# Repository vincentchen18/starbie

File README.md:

# Starbie

## Overview

Starbie is a tiny motion controlled desktop pet, powered by USB or battery. It is a star-shaped PCB hosting a little digital creature on an OLED Screen. It includes multiple interactive functionalities. Tilt it to navigate menus, shake it to wake it up, and watch its mood light change as you neglect it. (you probably shouldn't neglect it but this is also a functionality, not a recommendation.) Also has multiple sensors that track gyroscopic and accelerometric position, as well as tracking temperature and humidity.

This project was built for Hack Club's hardware program [Half Life](https://halflife.hackclub.com/), a 10 week YSWS to help beginners learn hardware project, and incidentally, it is ***my*** first hardware project!!! :DDD

I will also note that this is based off a tutorial from one of Half Life's organisers, and you can find the tutorial repo [here](https://github.com/SharKingStudios/Starbie). I added some additional features myself, but thank you [SharKingStudios](https://github.com/SharKingStudios/) this tutorial as it was a great starting point.

Additionally, I have also created a storage case for Starbie (although it is irregularly shaped due to how I shaped the printed circuit board)

## Schematic, PCB and Components

The final schematic is shown in the above picture, featuring a XIAO-ESP32-C3, Environment and MPU6050 sensor, as well as a menu button and an on/off switch as well as a battery connector. 

The desktop pet can be powered both by battery or by USB connection

## Features

- **Wandering pet:** a 32×32 pixel creature walks across the OLED.
- **Tilt-controlled radial menu:** press the menu button, then tilt to pick an option, and press again to select the option. The interactive options are:
- --> **Nap:** Starbie just falls asleep with zzz's until you shake it to wake it up
- --> **Play:** Starbie sprints in laps with hearts
- --> **Feed:** Starbie wiggles and jumps and gains fullness
- --> **Pet:** Increases Starbie's joy
- **Stats:** Joy, Energy, and Fullness, saved to flash so they save when you turn Starbie back on
- **Shake to wake:** shaking it wakes it and gets a reaction
- **Environment sensing:** Starbie can detect the temperature (and it **will** complain if it's too hot or cold!)
- **RGB Mood Light**: this shows how starbie is feeling:
Dark blue: napping
Pink: being loved
Red: too hot!
ice blue: too cold!
amber: hungry or tired
green: happy (brighter = morer happierness)
purple: dizzy

## Hardware

A storage case for Starbie has also been included, and you can find the box and lid STEP files in [`3D Models`](3D%20Models/)

Full list in [`BOM.csv`](Starbie/BOM.csv). Gerbers in [`gerbers/`](Starbie/gerbers/).

## Firmware

Arduino IDE was used to program Starbie.

## AI Usage

AI was not used in any way for this project besides as a guide to help me learn to use KiCad

## Bill of Materials

### Grant-funded ($30 tier 1)

| Item | Purpose | Qty | Unit (USD) | Total (USD) | Link |
|---|---|---|---|---|---|
| Starbie PCB (2-layer, 97.3×140.3mm) | Custom star-shaped board | 5 | 2.12 | 10.60 | [JLCPCB](https://jlcpcb.com/quote) |
| JLCPCB New User PCB coupon | Discount | 1 | -6.00 | -6.00 | — |
| JLCPCB shipping (Global Standard Direct Line → AU) | Shipping | 1 | 8.52 | 8.52 | [JLCPCB](https://jlcpcb.com/quote) |
| Seeed Studio XIAO ESP32-C3 | Main microcontroller | 1 | 6.31 | 6.31 | [AliExpress](https://www.aliexpress.com/item/1005008791664713.html) |
| 0.96" 128×64 I2C OLED (SSD1306) | Display | 1 | 2.20 | 2.20 | [AliExpress](https://www.aliexpress.com/item/1005006262908701.html) |
| DHT11 (bare 4-pin) | Temp + humidity sensor | 1 | 1.60 | 1.60 | [AliExpress](https://www.aliexpress.com/item/1005008818897051.html) |
| MPU-6050 (GY-521) | Accelerometer/gyro for tilt + shake | 1 | 1.03 | 1.03 | [AliExpress](https://www.aliexpress.com/item/1005008604349573.html) |
| 5mm RGB LED, common cathode (pack) | Mood light | 1 | 2.17 | 2.17 | [AliExpress](https://www.aliexpress.com/item/32601543257.html) |
| Resistor kit, 1/4W 300pcs (10k + 220Ω used) | DHT11 pull-up + LED current limiting | 1 | 3.23 | 3.23 | [AliExpress](https://www.aliexpress.com/item/1005011772534173.html) |
| **Grant total** | | | | **29.66** | |

### Paid out of pocket

| Item | Purpose | Qty | Unit (USD) | Total (USD) | Link |
|---|---|---|---|---|---|
| Gateron G Pro 3.0 MX switches (pack) | MENU + STATS buttons | 1 | 4.02 | 4.02 | [AliExpress](https://www.aliexpress.com/item/1005010559544082.html) |
| AliExpress shipping + 10% GST | Shipping + tax | 1 | 6.51 | 6.51 | — |
| **Out-of-pocket total** | | | | **10.53** | |

**Project total: $40.19**

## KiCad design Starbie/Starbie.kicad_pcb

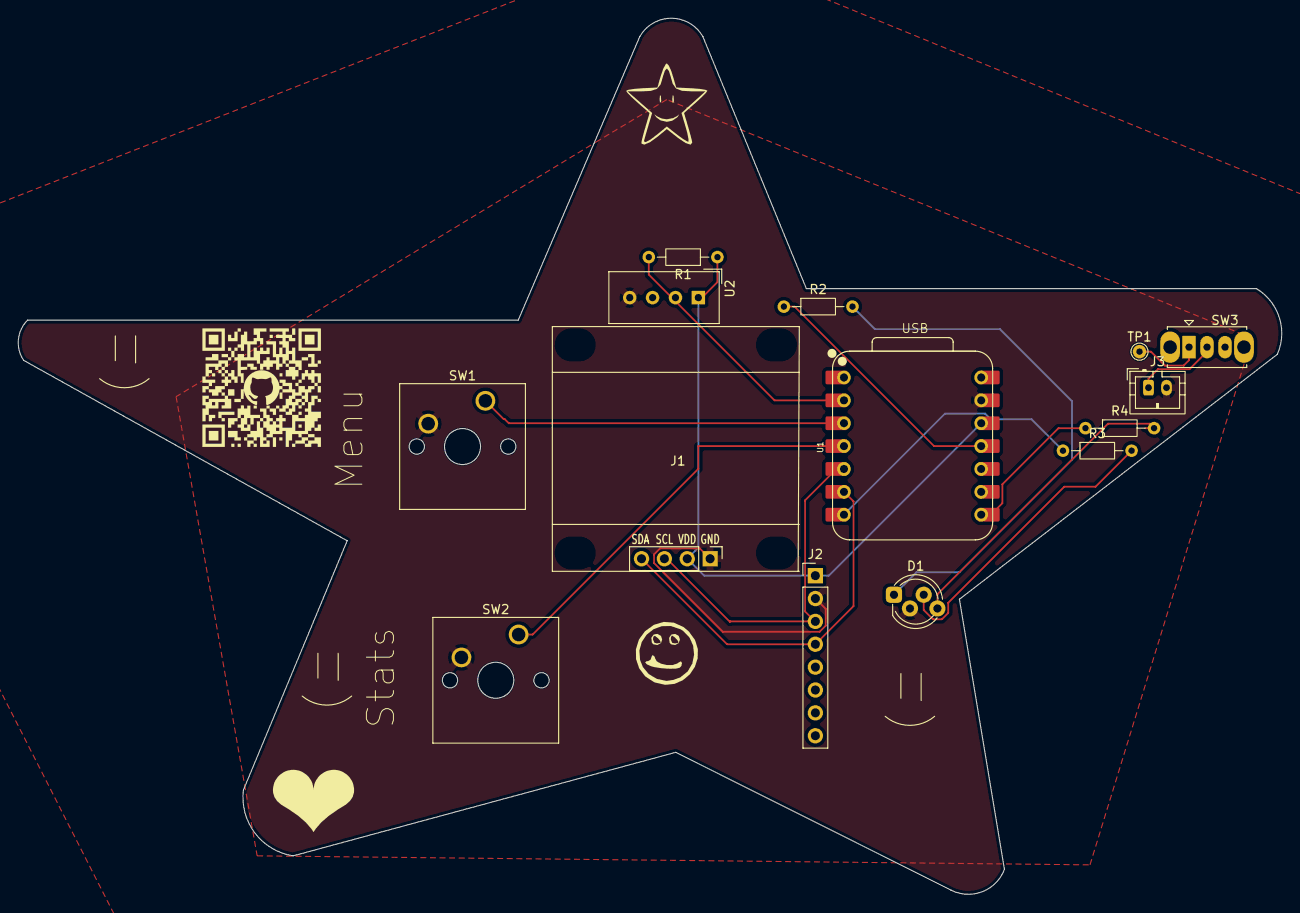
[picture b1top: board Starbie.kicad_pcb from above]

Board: 2 copper layers, 140.3 x 97.3 mm, 14 parts (0 on the bottom side), 15 nets.

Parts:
D1: LED_RKGB; LED_D5.0mm-4_RGB_Staggered_Pins
J1: Conn_01x04_Pin; Display_128x64_096_I2C
J2: Conn_01x08_Pin; PinHeader_1x08_P2.54mm_Vertical
J3: Conn_01x02_Socket; JST_PH_B2B-PH-K_1x02_P2.00mm_Vertical
R1: 10k; R_Axial_DIN0204_L3.6mm_D1.6mm_P7.62mm_Horizontal
R2, R3, R4: 220; R_Axial_DIN0204_L3.6mm_D1.6mm_P7.62mm_Horizontal
SW1, SW2: SW_Push; SW_Cherry_MX_1.00u_PCB
SW3: SW_SPDT; SW_Slide_SPDT_Straight_CK_OS102011MS2Q
TP1: TestPoint; TestPoint_THTPad_D1.5mm_Drill0.7mm
U1: XIAO-ESP32-C3-SMD; XIAO-ESP32-C6-DIP
U2: DHT11; Aosong_DHT11_5.5x12.0_P2.54mm

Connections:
+3.3V: J1.2, J2.1, R1.1, U1.12 (3V3_OUT), U2.1 (VDD)
/BAT_RAW: J3.1, SW3.2 (B)
/DHT11 DATA: R1.2, U1.2 (D1), U2.2 (DATA)
/GPIO2: SW1.1, U1.3 (D2)
/GPIO3: SW2.1, U1.4 (D3)
/LED_B: R4.1, U1.8 (D7)
/LED_G: R3.1, U1.7 (D6)
/LED_R: R2.1, U1.11 (D10)
/SCL: J1.3, J2.3, U1.5 (D4)
/SDA: J1.4, J2.4, U1.6 (D5)
/VBAT_SW: SW3.1 (A), TP1.1 (1_1)
GND: D1.2 (K), J1.1, J2.2, J3.2, SW1.2, SW2.2, U1.13 (GND), U2.4 (GND)
unnamed: D1.4 (BA), R4.2
unnamed: D1.3 (GA), R3.2
unnamed: D1.1 (RA), R2.2

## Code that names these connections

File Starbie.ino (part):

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const int BUTTON_ONE_PIN = 4;    // XIAO D2: opens/confirms the radial menu
const int BUTTON_TWO_PIN = 5;    // XIAO D3: shows/hides stats

const int LED_R_PIN = 10; // light pins
const int LED_G_PIN = 21;
const int LED_B_PIN = 20;

// Set this to false if your submission does not have a DHT11.
const bool USE_DHT11 = true;
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}

void setLight(int r, int g, int b) {
  analogWrite(LED_R_PIN, r); // turn on the lights for each light
  analogWrite(LED_G_PIN, g);
  analogWrite(LED_B_PIN, b);
}

void updateMoodLight() {
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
